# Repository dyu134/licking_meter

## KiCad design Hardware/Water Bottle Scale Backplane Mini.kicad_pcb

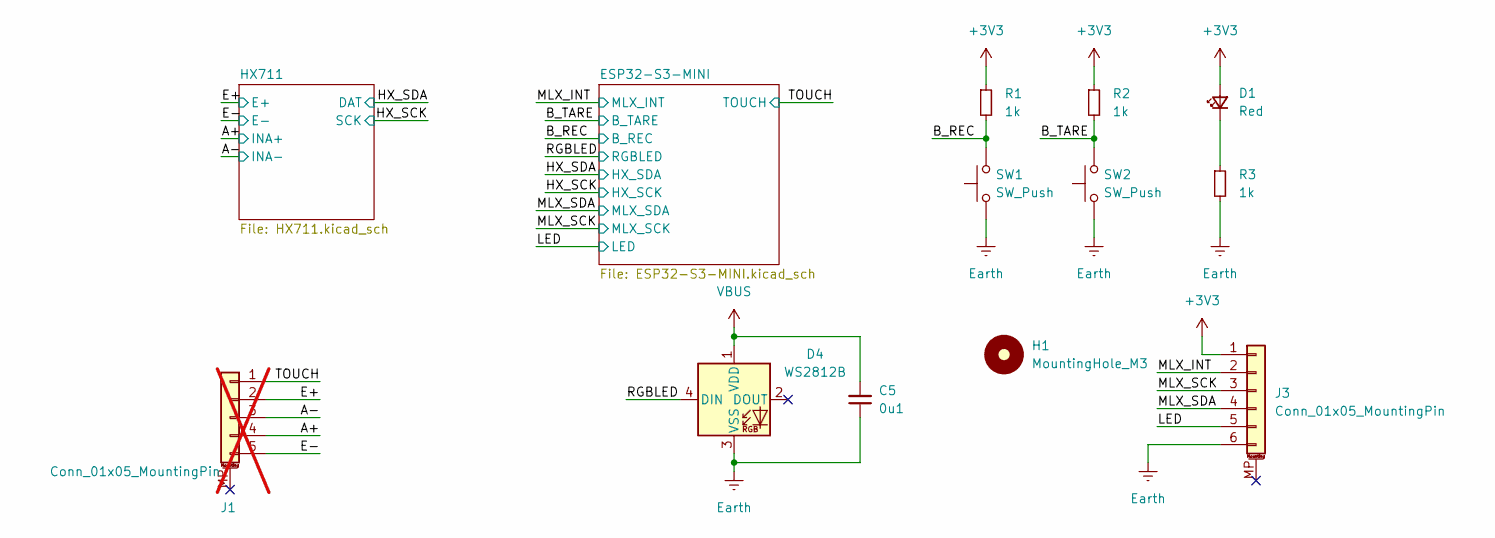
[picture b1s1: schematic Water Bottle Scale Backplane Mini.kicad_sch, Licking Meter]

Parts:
C5: 0u1; C_0402_1005Metric
D1: Red; LED_0603_1608Metric
D4: WS2812B; LED_WS2812B_PLCC4_5.0x5.0mm_P3.2mm
H1: MountingHole_M3; MountingHole_3.2mm_M3
J1: Conn_01x05_MountingPin; Molex_PicoBlade_53261-0571_1x05-1MP_P1.25mm_Horizontal; not fitted
J3: Conn_01x05_MountingPin; AFH34-S06FIA-1H
R1, R2, R3: 1k; R_0402_1005Metric
SW1, SW2: SW_Push; SW_SPST_EVQP7A

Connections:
+3V3: D1.2 (A), J3.1, R1.1, R2.1; also elsewhere on the board
/A+: J1.4; also elsewhere on the board
/A-: J1.3; also elsewhere on the board
/B_REC: R1.2, SW1.2; also elsewhere on the board
/B_TARE: R2.2, SW2.2; also elsewhere on the board
/E+: J1.2; also elsewhere on the board
/LED: J3.5; also elsewhere on the board
/MLX_INT: J3.2; also elsewhere on the board
/MLX_SCK: J3.3; also elsewhere on the board
/MLX_SDA: J3.4; also elsewhere on the board
/RGBLED: D4.4 (DIN); also elsewhere on the board
/TOUCH: J1.1; also elsewhere on the board
Earth: C5.1, D4.3 (VSS), J1.5, J3.6, R3.2, SW1.1, SW2.1; also elsewhere on the board
unnamed: D1.1 (K), R3.1
VBUS: C5.2, D4.1 (VDD); also elsewhere on the board

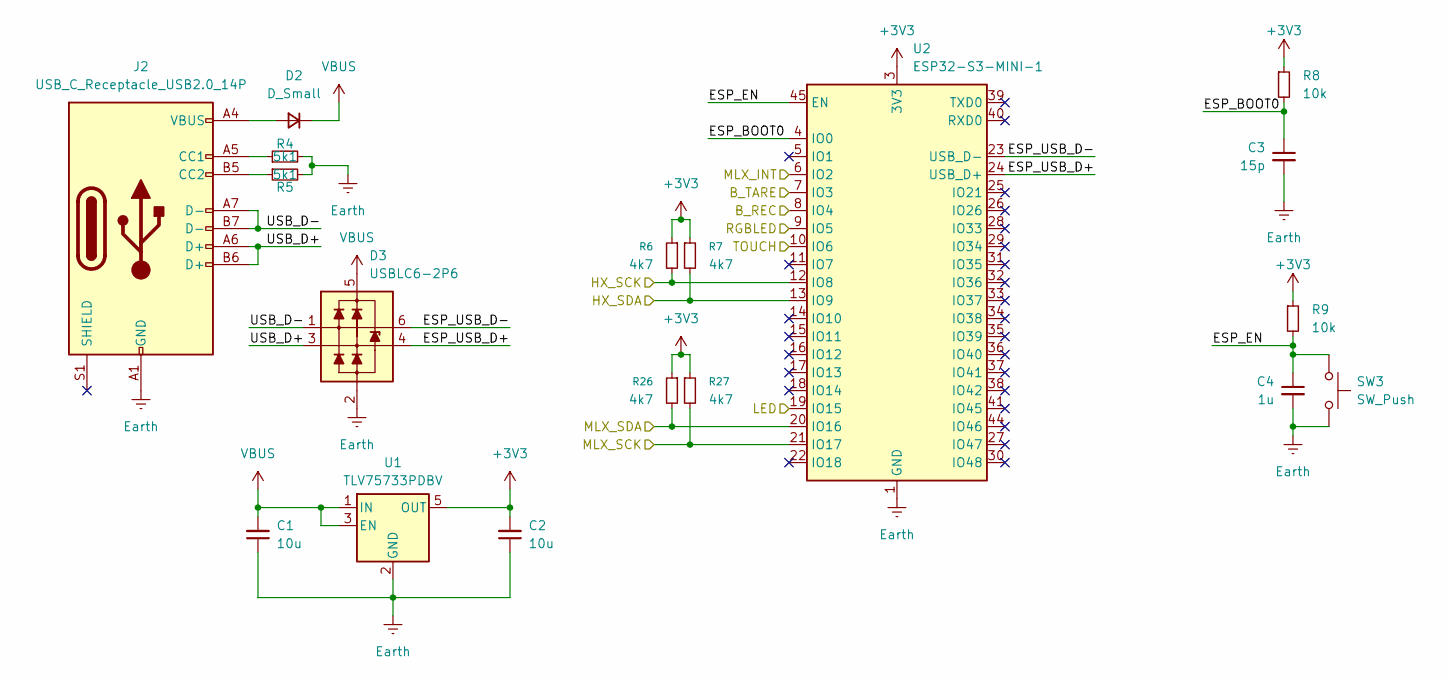
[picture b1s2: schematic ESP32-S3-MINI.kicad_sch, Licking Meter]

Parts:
C1, C2: 10u; C_0402_1005Metric
C3: 15p; C_0402_1005Metric; LCSC Part No. C85891
C4: 1u; C_0402_1005Metric; LCSC Part No. C85891
D2: D_Small; D_SOD-123
D3: USBLC6-2P6; SOT-666
J2: USB_C_Receptacle_USB2.0_14P; USB_C_Receptacle_GCT_USB4105-xx-A_16P_TopMnt_Horizontal
R4, R5: 5k1; R_0402_1005Metric
R6, R7, R26, R27: 4k7; R_0402_1005Metric
R8, R9: 10k; R_0402_1005Metric; LCSC Part No. C106225
SW3: SW_Push; SW_SPST_EVQP7A
U1: TLV75733PDBV; SOT-23-5
U2: ESP32-S3-MINI-1; ESP32-S2-MINI-1

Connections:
+3V3: C2.2, R6.1, R7.1, R8.1, R9.1, R26.1, R27.1, U1.5 (OUT), U2.3 (3V3); also elsewhere on the board
/B_REC: U2.8 (IO4); also elsewhere on the board
/B_TARE: U2.7 (IO3); also elsewhere on the board
/ESP32-S3-MINI/ESP_BOOT0: C3.1, R8.2, U2.4 (IO0)
/ESP32-S3-MINI/ESP_EN: C4.1, R9.2, SW3.1, U2.45 (EN)
/ESP32-S3-MINI/ESP_USB_D+: D3.4 (L2), U2.24 (USB_D+)
/ESP32-S3-MINI/ESP_USB_D-: D3.6 (L1), U2.23 (USB_D-)
/ESP32-S3-MINI/USB_D+: D3.3 (L2), J2.A6 (D+), J2.B6 (D+)
/ESP32-S3-MINI/USB_D-: D3.1 (L1), J2.A7 (D-), J2.B7 (D-)
/HX_SCK: R6.2, U2.12 (IO8); also elsewhere on the board
/HX_SDA: R7.2, U2.13 (IO9); also elsewhere on the board
/LED: U2.19 (IO15); also elsewhere on the board
/MLX_INT: U2.6 (IO2); also elsewhere on the board
/MLX_SCK: R27.2, U2.21 (IO17); also elsewhere on the board
/MLX_SDA: R26.2, U2.20 (IO16); also elsewhere on the board
/RGBLED: U2.9 (IO5); also elsewhere on the board
/TOUCH: U2.10 (IO6); also elsewhere on the board
Earth: C1.1, C2.1, C3.2, C4.2, D3.2 (VN), J2.A1 (GND), J2.A12 (GND), J2.B1 (GND), J2.B12 (GND), R4.2, R5.2, SW3.2, U1.2 (GND), U2.1 (GND), U2.2 (GND), U2.42 (GND), U2.43 (GND), U2.46 (GND), U2.47 (GND), U2.48 (GND), U2.49 (GND), U2.50 (GND), U2.51 (GND), U2.52 (GND), U2.53 (GND), U2.54 (GND), U2.55 (GND), U2.56 (GND), U2.57 (GND), U2.58 (GND), U2.59 (GND), U2.60 (GND), U2.61 (GND), U2.62 (GND), U2.63 (GND), U2.64 (GND), U2.65 (GND); also elsewhere on the board
unnamed: D2.2 (A), J2.A4 (VBUS), J2.A9 (VBUS), J2.B4 (VBUS), J2.B9 (VBUS)
unnamed: J2.A5 (CC1), R4.1
unnamed: J2.B5 (CC2), R5.1
VBUS: C1.2, D2.1 (K), D3.5 (VP), U1.1 (IN), U1.3 (EN); also elsewhere on the board

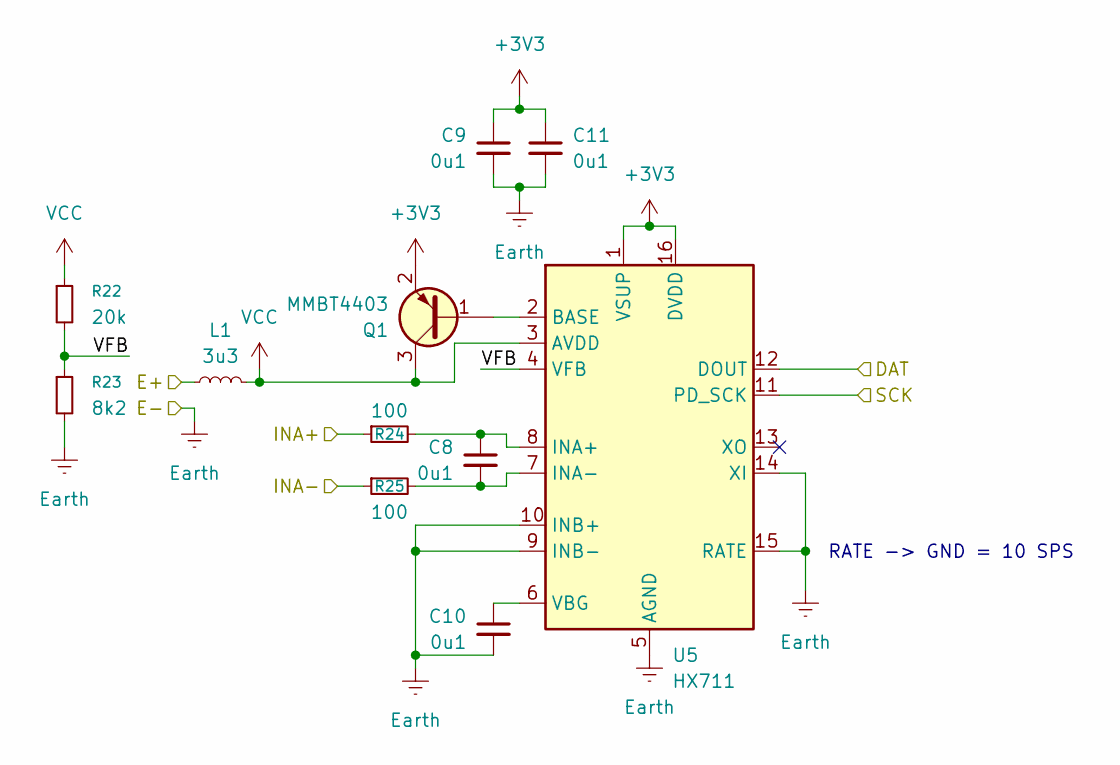
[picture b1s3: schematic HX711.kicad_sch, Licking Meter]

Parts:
C8, C9, C10, C11: 0u1; C_0402_1005Metric
L1: 3u3; L_0402_1005Metric
Q1: MMBT4403; SOT-23
R22: 20k; R_0402_1005Metric
R23: 8k2; R_0402_1005Metric
R24, R25: 100; R_0402_1005Metric
U5: HX711; SOIC-16_3.9x9.9mm_P1.27mm

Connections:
+3V3: C9.1, C11.1, Q1.2 (E), U5.1 (VSUP), U5.16 (DVDD); also elsewhere on the board
/A+: R24.1; also elsewhere on the board
/A-: R25.1; also elsewhere on the board
/E+: L1.1; also elsewhere on the board
/HX711/VFB: R22.2, R23.1, U5.4 (VFB)
/HX_SCK: U5.11 (PD_SCK); also elsewhere on the board
/HX_SDA: U5.12 (DOUT); also elsewhere on the board
Earth: C9.2, C10.2, C11.2, R23.2, U5.5 (AGND), U5.9 (INB-), U5.10 (INB+), U5.14 (XI), U5.15 (RATE); also elsewhere on the board
unnamed: Q1.1 (B), U5.2 (BASE)
unnamed: C8.1, R24.2, U5.8 (INA+)
unnamed: C8.2, R25.2, U5.7 (INA-)
unnamed: C10.1, U5.6 (VBG)
VCC: L1.2, Q1.3 (C), R22.1, U5.3 (AVDD)

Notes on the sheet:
RATE -> GND = 10 SPS

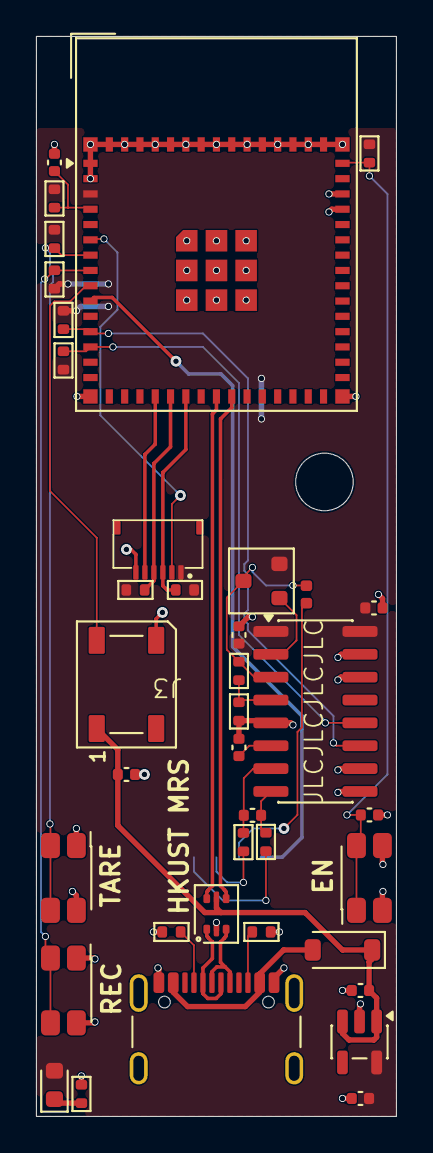
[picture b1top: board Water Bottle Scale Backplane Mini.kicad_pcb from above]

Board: 2 copper layers, 20.0 x 60.0 mm, 40 parts (1 on the bottom side), 32 nets.

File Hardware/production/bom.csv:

Designator,Footprint,Quantity,Value,LCSC Part #
"C1, C2",0402,2,10u,
"C10, C11, C5, C8, C9",0402,5,0u1,
C3,0402,1,15p,C85891
C4,0402,1,1u,C85891
D1,0603,1,Red,
D2,D_SOD-123,1,D_Small,
D3,SOT-666,1,USBLC6-2P6,
D4,LED_WS2812B_PLCC4_5.0x5.0mm_P3.2mm,1,WS2812B,
J2,USB_C_Receptacle_GCT_USB4105-xx-A_16P_TopMnt_Horizontal,1,USB_C_Receptacle_USB2.0_14P,
J3,AFH34-S06FIA-1H,1,Conn_01x05_MountingPin,
L1,0402,1,3u3,
Q1,SOT-23,1,MMBT4403,
"R1, R2, R3",0402,3,1k,
R22,0402,1,20k,
R23,0402,1,8k2,
"R24, R25",0402,2,100,
"R26, R27, R6, R7",0402,4,4k7,
"R4, R5",0402,2,5k1,
"R8, R9",0402,2,10k,C106225
"SW1, SW2, SW3",SW_SPST_EVQP7A,3,SW_Push,
U1,SOT-23-5,1,TLV75733PDBV,
U2,ESP32-S2-MINI-1,1,ESP32-S3-MINI-1,
U5,SOIC-16_3.9x9.9mm_P1.27mm,1,HX711,
